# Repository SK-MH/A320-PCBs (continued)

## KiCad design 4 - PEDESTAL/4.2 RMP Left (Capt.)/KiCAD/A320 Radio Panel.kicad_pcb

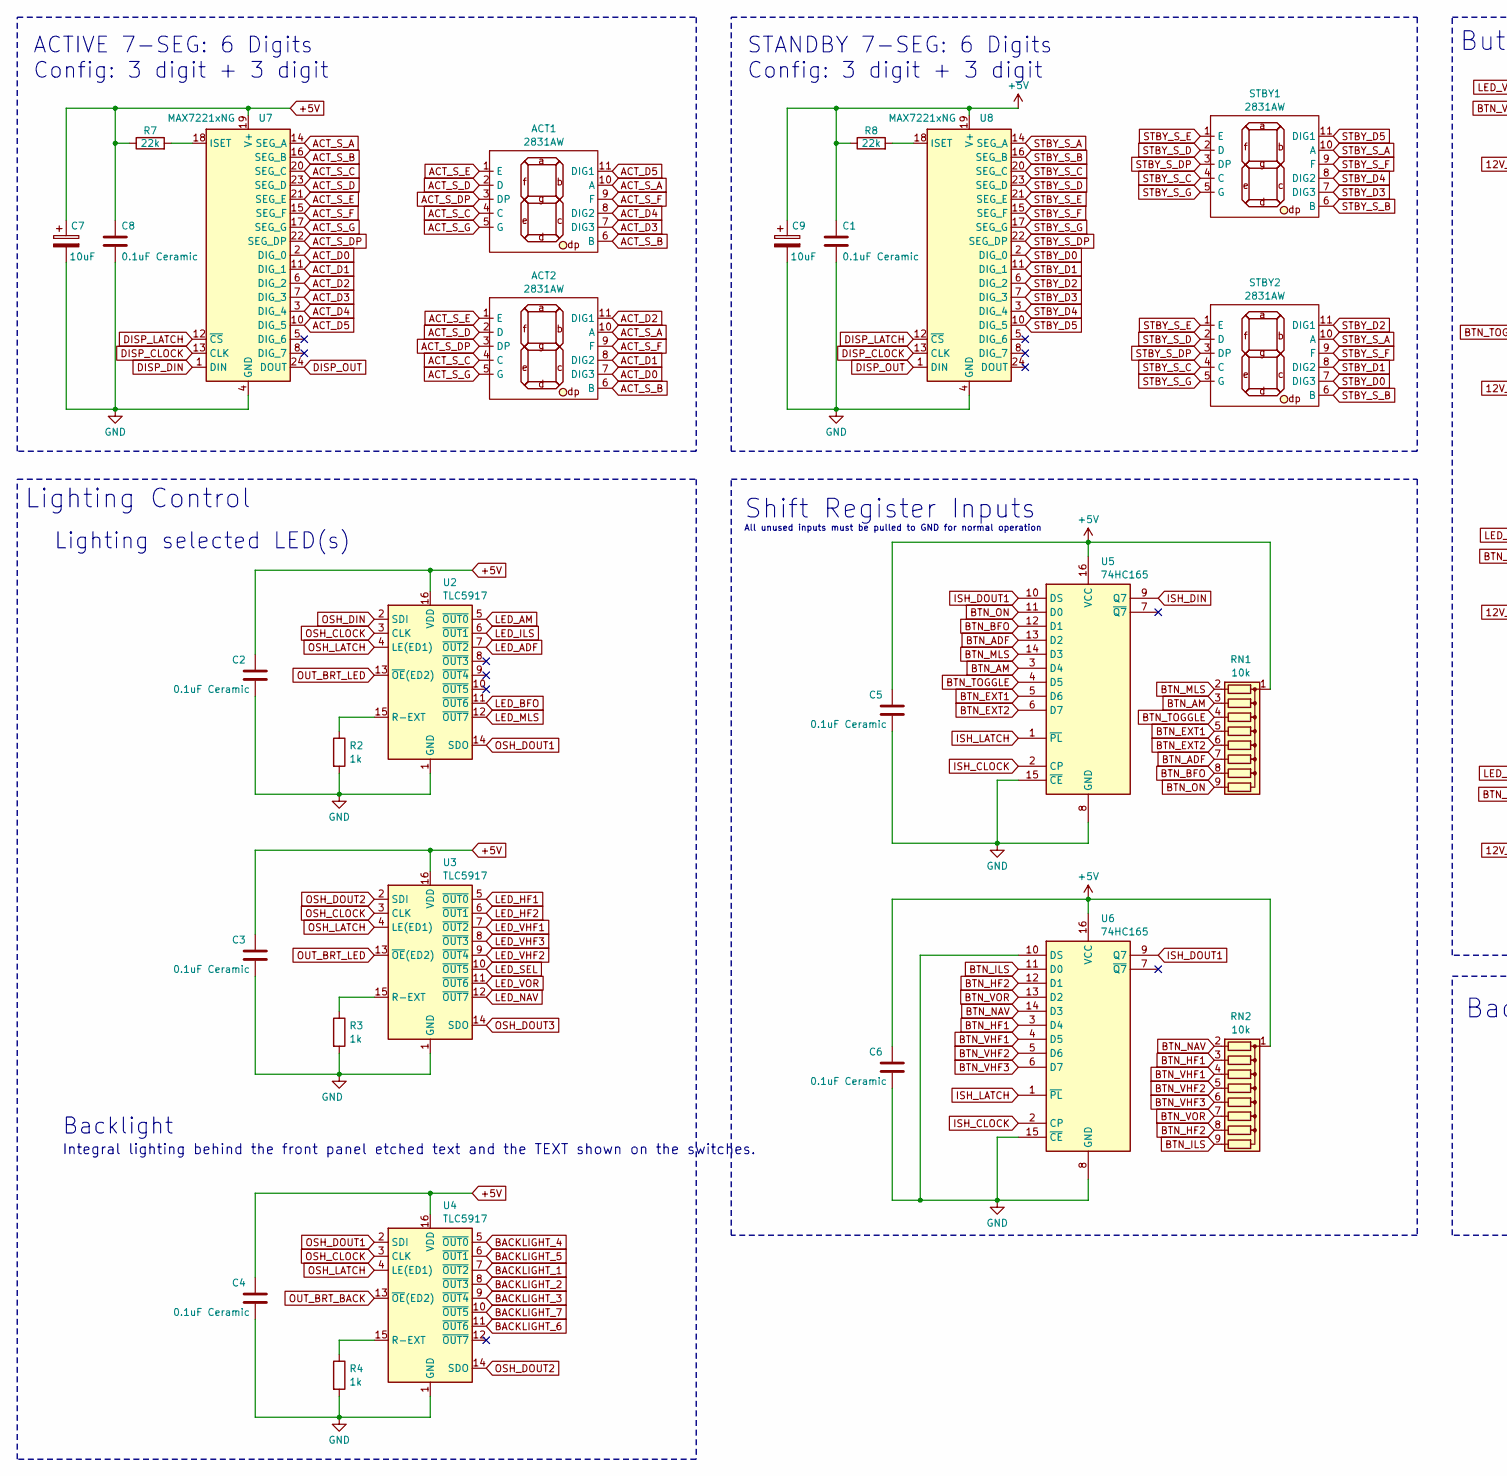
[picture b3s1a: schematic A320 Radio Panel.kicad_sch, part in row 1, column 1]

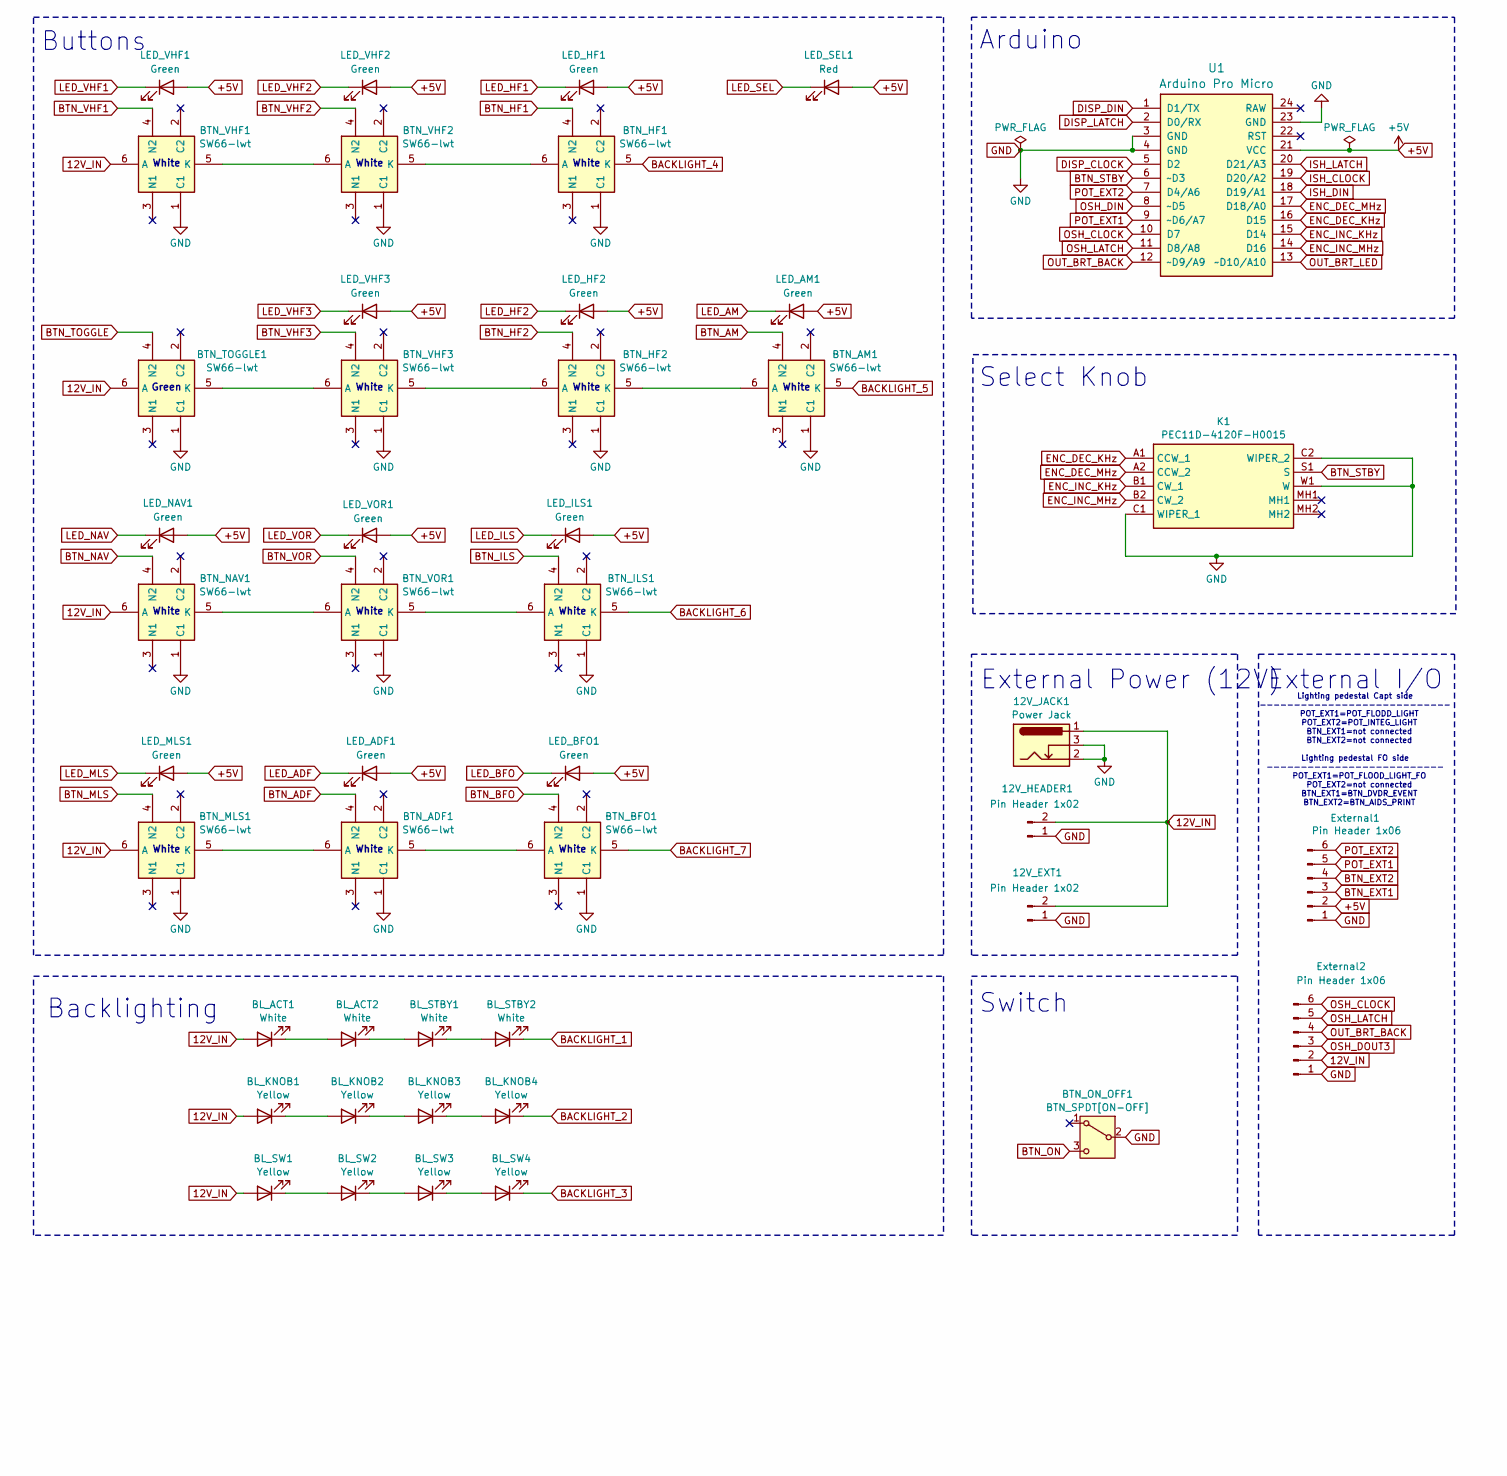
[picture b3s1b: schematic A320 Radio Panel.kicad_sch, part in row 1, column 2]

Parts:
12V_EXT1, 12V_HEADER1: Pin Header 1x02; JST_EH_B2B-EH-A_1x02_P2.50mm_Vertical
12V_JACK1: Power Jack; BarrelJack_Horizontal
ACT1, ACT2: 2831AW
BL_ACT1, BL_ACT2: White; LED_D3.0mm
BL_KNOB1, BL_KNOB2, BL_KNOB3, BL_KNOB4: Yellow; LED_D3.0mm
BL_STBY1, BL_STBY2: White; LED_D3.0mm
BL_SW1, BL_SW2, BL_SW3, BL_SW4: Yellow; LED_D3.0mm
BTN_ADF1: SW66-lwt
BTN_AM1: SW66-lwt
BTN_BFO1: SW66-lwt
BTN_HF1, BTN_HF2: SW66-lwt
BTN_ILS1: SW66-lwt
BTN_MLS1: SW66-lwt
BTN_NAV1: SW66-lwt
BTN_ON_OFF1: BTN_SPDT[ON-OFF]; T80-Z1
BTN_TOGGLE1: SW66-lwt
BTN_VHF1, BTN_VHF2, BTN_VHF3: SW66-lwt
BTN_VOR1: SW66-lwt
C1, C2, C3, C4, C5, C6, C8: 0.1uF Ceramic; C_Disc_D3.0mm_W1.6mm_P2.50mm
C7, C9: 10uF; CP_Radial_D4.0mm_P1.50mm
External1, External2: Pin Header 1x06; JST_EH_B6B-EH-A_1x06_P2.50mm_Vertical
K1: PEC11D-4120F-H0015; PEC11D4120FH0015; Mouser Part Number 652-PEC11D4120FH0015
LED_ADF1: Green; LED_D3.0mm
LED_AM1: Green; LED_D3.0mm
LED_BFO1: Green; LED_D3.0mm
LED_HF1, LED_HF2: Green; LED_D3.0mm
LED_ILS1: Green; LED_D3.0mm
LED_MLS1: Green; LED_D3.0mm
LED_NAV1: Green; LED_D3.0mm
LED_SEL1: Red; LED_D3.0mm
LED_VHF1, LED_VHF2, LED_VHF3: Green; LED_D3.0mm
LED_VOR1: Green; LED_D3.0mm
R2, R3, R4: 1k; R_Axial_DIN0204_L3.6mm_D1.6mm_P7.62mm_Horizontal
R7, R8: 22k; R_Axial_DIN0204_L3.6mm_D1.6mm_P7.62mm_Horizontal
RN1, RN2: 10k; R_Array_SIP9
STBY1, STBY2: 2831AW
U1: Arduino Pro Micro; Sparkfun_Pro_Micro
U2, U3, U4: TLC5917; DIP-16_W7.62mm
U5, U6: 74HC165; DIP-16_W7.62mm
U7, U8: MAX7221xNG; DIP-24_W7.62mm

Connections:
12V_IN: 12V_EXT1.2, 12V_HEADER1.2, 12V_JACK1.1, BL_ACT1.2 (A), BL_KNOB1.2 (A), BL_SW1.2 (A), BTN_MLS1.6 (A), BTN_NAV1.6 (A), BTN_TOGGLE1.6 (A), BTN_VHF1.6 (A), External2.2
+5V: C1.1, C2.1, C3.1, C4.1, C5.1, C6.1, C7.1, C8.1, C9.1, External1.2, LED_ADF1.2 (A), LED_AM1.2 (A), LED_BFO1.2 (A), LED_HF1.2 (A), LED_HF2.2 (A), LED_ILS1.2 (A), LED_MLS1.2 (A), LED_NAV1.2 (A), LED_SEL1.2 (A), LED_VHF1.2 (A), LED_VHF2.2 (A), LED_VHF3.2 (A), LED_VOR1.2 (A), R7.1, R8.1, RN1.1 (common), RN2.1 (common), U1.21 (VCC), U2.16 (VDD), U3.16 (VDD), U4.16 (VDD), U5.16 (VCC), U6.16 (VCC), U7.19 (V+), U8.19 (V+)
ACT_D0: ACT2.7 (DIG3), U7.2 (DIG_0)
ACT_D1: ACT2.8 (DIG2), U7.11 (DIG_1)
ACT_D2: ACT2.11 (DIG1), U7.6 (DIG_2)
ACT_D3: ACT1.7 (DIG3), U7.7 (DIG_3)
ACT_D4: ACT1.8 (DIG2), U7.3 (DIG_4)
ACT_D5: ACT1.11 (DIG1), U7.10 (DIG_5)
ACT_S_A: ACT1.10 (A), ACT2.10 (A), U7.14 (SEG_A)
ACT_S_B: ACT1.6 (B), ACT2.6 (B), U7.16 (SEG_B)
ACT_S_C: ACT1.4 (C), ACT2.4 (C), U7.20 (SEG_C)
ACT_S_D: ACT1.2 (D), ACT2.2 (D), U7.23 (SEG_D)
ACT_S_DP: ACT1.3 (DP), ACT2.3 (DP), U7.22 (SEG_DP)
ACT_S_E: ACT1.1 (E), ACT2.1 (E), U7.21 (SEG_E)
ACT_S_F: ACT1.9 (F), ACT2.9 (F), U7.15 (SEG_F)
ACT_S_G: ACT1.5 (G), ACT2.5 (G), U7.17 (SEG_G)
BACKLIGHT_1: BL_STBY2.1 (K), U4.7 (~OUT2)
BACKLIGHT_2: BL_KNOB4.1 (K), U4.8 (~OUT3)
BACKLIGHT_3: BL_SW4.1 (K), U4.9 (~OUT4)
BACKLIGHT_4: BTN_HF1.5 (K), U4.5 (~OUT0)
BACKLIGHT_5: BTN_AM1.5 (K), U4.6 (~OUT1)
BACKLIGHT_6: BTN_ILS1.5 (K), U4.11 (~OUT6)
BACKLIGHT_7: BTN_BFO1.5 (K), U4.10 (~OUT5)
BTN_ADF: BTN_ADF1.4 (N2), RN1.7 (R6), U5.13 (D2)
BTN_AM: BTN_AM1.4 (N2), RN1.3 (R2), U5.3 (D4)
BTN_BFO: BTN_BFO1.4 (N2), RN1.8 (R7), U5.12 (D1)
BTN_EXT1: External1.3, RN1.5 (R4), U5.5 (D6)
BTN_EXT2: External1.4, RN1.6 (R5), U5.6 (D7)
BTN_HF1: BTN_HF1.4 (N2), RN2.3 (R2), U6.3 (D4)
BTN_HF2: BTN_HF2.4 (N2), RN2.8 (R7), U6.12 (D1)
BTN_ILS: BTN_ILS1.4 (N2), RN2.9 (R8), U6.11 (D0)
BTN_MLS: BTN_MLS1.4 (N2), RN1.2 (R1), U5.14 (D3)
BTN_NAV: BTN_NAV1.4 (N2), RN2.2 (R1), U6.14 (D3)
BTN_ON: BTN_ON_OFF1.3 (C), RN1.9 (R8), U5.11 (D0)
BTN_STBY: K1.S1 (S), U1.6 (~D3)
BTN_TOGGLE: BTN_TOGGLE1.4 (N2), RN1.4 (R3), U5.4 (D5)
BTN_VHF1: BTN_VHF1.4 (N2), RN2.4 (R3), U6.4 (D5)
BTN_VHF2: BTN_VHF2.4 (N2), RN2.5 (R4), U6.5 (D6)
BTN_VHF3: BTN_VHF3.4 (N2), RN2.6 (R5), U6.6 (D7)
BTN_VOR: BTN_VOR1.4 (N2), RN2.7 (R6), U6.13 (D2)
DISP_CLOCK: U1.5 (D2), U7.13 (CLK), U8.13 (CLK)
DISP_DIN: U1.1 (D1/TX), U7.1 (DIN)
DISP_LATCH: U1.2 (D0/RX), U7.12 (~CS), U8.12 (~CS)
DISP_OUT: U7.24 (DOUT), U8.1 (DIN)
ENC_DEC_KHz: K1.A1 (CCW_1), U1.16 (D15)
ENC_DEC_MHz: K1.A2 (CCW_2), U1.17 (D18/A0)
ENC_INC_KHz: K1.B1 (CW_1), U1.15 (D14)
ENC_INC_MHz: K1.B2 (CW_2), U1.14 (D16)
GND: 12V_EXT1.1, 12V_HEADER1.1, 12V_JACK1.2, 12V_JACK1.3, BTN_ADF1.1 (C1), BTN_AM1.1 (C1), BTN_BFO1.1 (C1), BTN_HF1.1 (C1), BTN_HF2.1 (C1), BTN_ILS1.1 (C1), BTN_MLS1.1 (C1), BTN_NAV1.1 (C1), BTN_ON_OFF1.2 (B), BTN_TOGGLE1.1 (C1), BTN_VHF1.1 (C1), BTN_VHF2.1 (C1), BTN_VHF3.1 (C1), BTN_VOR1.1 (C1), C1.2, C2.2, C3.2, C4.2, C5.2, C6.2, C7.2, C8.2, C9.2, External1.1, External2.1, K1.C1 (WIPER_1), K1.C2 (WIPER_2), K1.W1 (W), R2.2, R3.2, R4.2, U1.3 (GND), U1.4 (GND), U1.23 (GND), U2.1 (GND), U3.1 (GND), U4.1 (GND), U5.8 (GND), U5.15 (~CE), U6.8 (GND), U6.10 (DS), U6.15 (~CE), U7.4 (GND), U7.9 (GND), U8.4 (GND), U8.9 (GND)
ISH_CLOCK: U1.19 (D20/A2), U5.2 (CP), U6.2 (CP)
ISH_DIN: U1.18 (D19/A1), U5.9 (Q7)
ISH_DOUT1: U5.10 (DS), U6.9 (Q7)
ISH_LATCH: U1.20 (D21/A3), U5.1 (~PL), U6.1 (~PL)
LED_ADF: LED_ADF1.1 (K), U2.7 (~OUT2)
LED_AM: LED_AM1.1 (K), U2.5 (~OUT0)
LED_BFO: LED_BFO1.1 (K), U2.11 (~OUT6)
LED_HF1: LED_HF1.1 (K), U3.5 (~OUT0)
LED_HF2: LED_HF2.1 (K), U3.6 (~OUT1)
LED_ILS: LED_ILS1.1 (K), U2.6 (~OUT1)
LED_MLS: LED_MLS1.1 (K), U2.12 (~OUT7)
LED_NAV: LED_NAV1.1 (K), U3.12 (~OUT7)
LED_SEL: LED_SEL1.1 (K), U3.10 (~OUT5)
LED_VHF1: LED_VHF1.1 (K), U3.7 (~OUT2)
LED_VHF2: LED_VHF2.1 (K), U3.9 (~OUT4)
LED_VHF3: LED_VHF3.1 (K), U3.8 (~OUT3)
LED_VOR: LED_VOR1.1 (K), U3.11 (~OUT6)
unnamed: BL_ACT1.1 (K), BL_ACT2.2 (A)
unnamed: BL_ACT2.1 (K), BL_STBY1.2 (A)
unnamed: BL_KNOB1.1 (K), BL_KNOB2.2 (A)
unnamed: BL_KNOB2.1 (K), BL_KNOB3.2 (A)
unnamed: BL_KNOB3.1 (K), BL_KNOB4.2 (A)
unnamed: BL_STBY1.1 (K), BL_STBY2.2 (A)
unnamed: BL_SW1.1 (K), BL_SW2.2 (A)
unnamed: BL_SW2.1 (K), BL_SW3.2 (A)
unnamed: BL_SW3.1 (K), BL_SW4.2 (A)
unnamed: BTN_ADF1.6 (A), BTN_MLS1.5 (K)
unnamed: BTN_ADF1.5 (K), BTN_BFO1.6 (A)
unnamed: BTN_AM1.6 (A), BTN_HF2.5 (K)
unnamed: BTN_HF1.6 (A), BTN_VHF2.5 (K)
unnamed: BTN_HF2.6 (A), BTN_VHF3.5 (K)
unnamed: BTN_ILS1.6 (A), BTN_VOR1.5 (K)
unnamed: BTN_NAV1.5 (K), BTN_VOR1.6 (A)
unnamed: BTN_TOGGLE1.5 (K), BTN_VHF3.6 (A)
unnamed: BTN_VHF1.5 (K), BTN_VHF2.6 (A)
unnamed: R2.1, U2.15 (R-EXT)
unnamed: R3.1, U3.15 (R-EXT)
unnamed: R4.1, U4.15 (R-EXT)
unnamed: R7.2, U7.18 (ISET)
unnamed: R8.2, U8.18 (ISET)
OSH_CLOCK: External2.6, U1.10 (D7), U2.3 (CLK), U3.3 (CLK), U4.3 (CLK)
OSH_DIN: U1.8 (~D5), U2.2 (SDI)
OSH_DOUT1: U2.14 (SDO), U4.2 (SDI)
OSH_DOUT2: U3.2 (SDI), U4.14 (SDO)
OSH_DOUT3: External2.3, U3.14 (SDO)
OSH_LATCH: External2.5, U1.11 (D8/A8), U2.4 (LE(ED1)), U3.4 (LE(ED1)), U4.4 (LE(ED1))
OUT_BRT_BACK: External2.4, U1.12 (~D9/A9), U4.13 (~OE(ED2))
OUT_BRT_LED: U1.13 (~D10/A10), U2.13 (~OE(ED2)), U3.13 (~OE(ED2))
POT_EXT1: External1.5, U1.9 (~D6/A7)
POT_EXT2: External1.6, U1.7 (D4/A6)
STBY_D0: STBY2.7 (DIG3), U8.2 (DIG_0)
STBY_D1: STBY2.8 (DIG2), U8.11 (DIG_1)
STBY_D2: STBY2.11 (DIG1), U8.6 (DIG_2)
STBY_D3: STBY1.7 (DIG3), U8.7 (DIG_3)
STBY_D4: STBY1.8 (DIG2), U8.3 (DIG_4)
STBY_D5: STBY1.11 (DIG1), U8.10 (DIG_5)
STBY_S_A: STBY1.10 (A), STBY2.10 (A), U8.14 (SEG_A)
STBY_S_B: STBY1.6 (B), STBY2.6 (B), U8.16 (SEG_B)
STBY_S_C: STBY1.4 (C), STBY2.4 (C), U8.20 (SEG_C)
STBY_S_D: STBY1.2 (D), STBY2.2 (D), U8.23 (SEG_D)
STBY_S_DP: STBY1.3 (DP), STBY2.3 (DP), U8.22 (SEG_DP)
STBY_S_E: STBY1.1 (E), STBY2.1 (E), U8.21 (SEG_E)
STBY_S_F: STBY1.9 (F), STBY2.9 (F), U8.15 (SEG_F)
STBY_S_G: STBY1.5 (G), STBY2.5 (G), U8.17 (SEG_G)

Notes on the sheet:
White
STANDBY 7-SEG: 6 Digits Config: 3 digit + 3 digit
Lighting selected LED(s)
Backlight
Buttons
Shift Register Inputs
Lighting Control
External I/O
Green
Integral lighting behind the front panel etched text and the TEXT shown on the switches.
Lighting pedestal Capt side ---------------------------- POT_EXT1=POT_FLODD_LIGHT POT_EXT2=POT_INTEG_LIGHT BTN_EXT1=not connected BTN_EXT2=not connected Lighting pedestal FO side -------------------------- POT_EXT1=POT_FLOOD_LIGHT_FO POT_EXT2=not connected BTN_EXT1=BTN_DVDR_EVENT BTN_EXT2=BTN_AIDS_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
Arduino
All unused inputs must be pulled to GND for normal operation
Switch
Select Knob
ACTIVE 7-SEG: 6 Digits Config: 3 digit + 3 digit
External Power (12V)
Backlighting

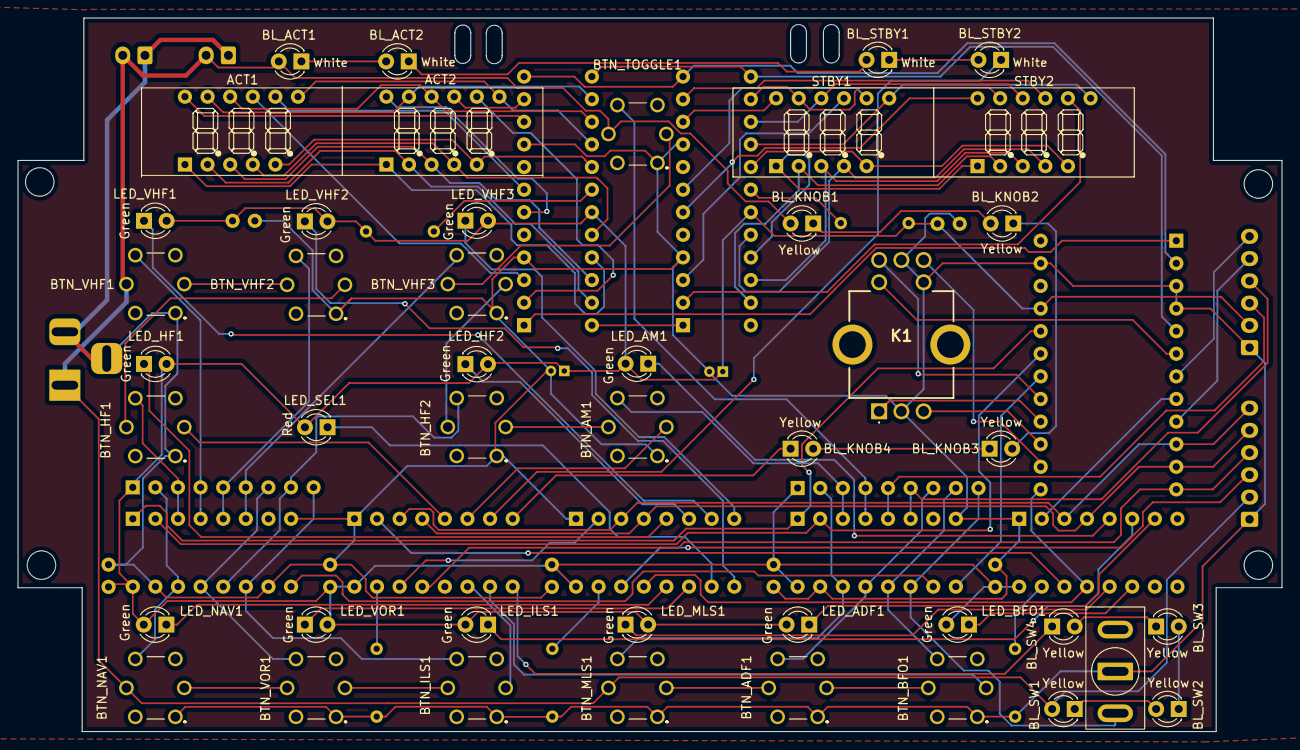
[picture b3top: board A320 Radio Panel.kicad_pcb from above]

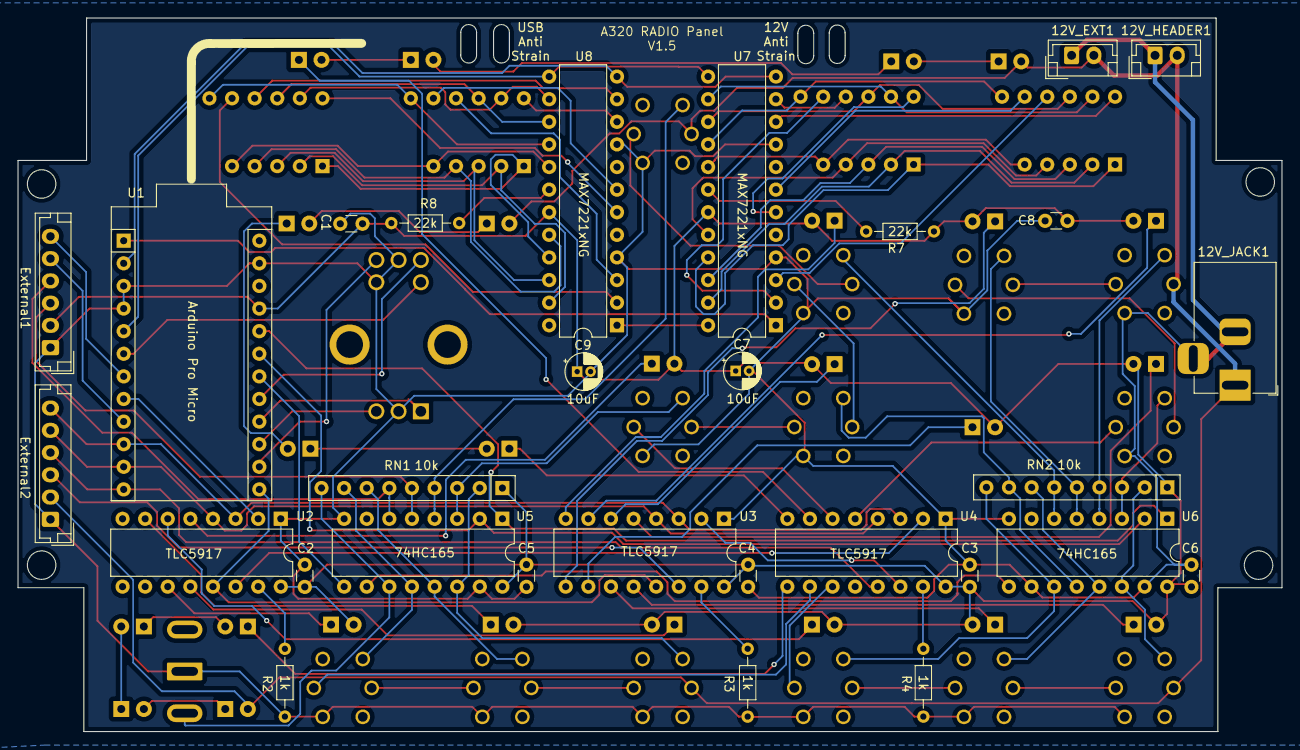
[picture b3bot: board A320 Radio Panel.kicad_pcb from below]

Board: 2 copper layers, 142.0 x 80.2 mm, 73 parts (29 on the bottom side), 113 nets.

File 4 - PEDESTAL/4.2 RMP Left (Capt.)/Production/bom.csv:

Designator,Footprint,Quantity,Value,LCSC Part #
"12V_EXT1, 12V_HEADER1",JST_EH_B2B-EH-A_1x02_P2.50mm_Vertical,2,Pin Header 1x02,
12V_JACK1,BarrelJack_Horizontal,1,Power Jack,
"ACT1, ACT2, STBY1, STBY2",2831AW,4,2831AW,
"BL_ACT1, BL_ACT2, BL_STBY1, BL_STBY2",LED_D3.0mm,4,White,
"BL_KNOB1, BL_KNOB2, BL_KNOB3, BL_KNOB4, BL_SW1, BL_SW2, BL_SW3, BL_SW4",LED_D3.0mm,8,Yellow,
"BTN_ADF1, BTN_AM1, BTN_BFO1, BTN_HF1, BTN_HF2, BTN_ILS1, BTN_MLS1, BTN_NAV1, BTN_TOGGLE1, BTN_VHF1, BTN_VHF2, BTN_VHF3, BTN_VOR1",SW66-lwt,13,SW66-lwt,
BTN_ON_OFF1,T80-Z1,1,BTN_SPDT[ON-OFF],
"C1, C2, C3, C4, C5, C6, C8",C_Disc_D3.0mm_W1.6mm_P2.50mm,7,0.1uF Ceramic,
"C7, C9",CP_Radial_D4.0mm_P1.50mm,2,10uF,
"External1, External2",JST_EH_B6B-EH-A_1x06_P2.50mm_Vertical,2,Pin Header 1x06,
K1,PEC11D4120FH0015,1,PEC11D-4120F-H0015,
"LED_ADF1, LED_AM1, LED_BFO1, LED_HF1, LED_HF2, LED_ILS1, LED_MLS1, LED_NAV1, LED_VHF1, LED_VHF2, LED_VHF3, LED_VOR1",LED_D3.0mm,12,Green,
LED_SEL1,LED_D3.0mm,1,Red,
"R2, R3, R4",R_Axial_DIN0204_L3.6mm_D1.6mm_P7.62mm_Horizontal,3,1k,
"R7, R8",R_Axial_DIN0204_L3.6mm_D1.6mm_P7.62mm_Horizontal,2,22k,
"RN1, RN2",R_Array_SIP9,2,10k,
U1,Sparkfun_Pro_Micro,1,Arduino Pro Micro,
"U2, U3, U4",DIP-16_W7.62mm,3,TLC5917,
"U5, U6",DIP-16_W7.62mm,2,74HC165,
"U7, U8",DIP-24_W7.62mm,2,MAX7221xNG,

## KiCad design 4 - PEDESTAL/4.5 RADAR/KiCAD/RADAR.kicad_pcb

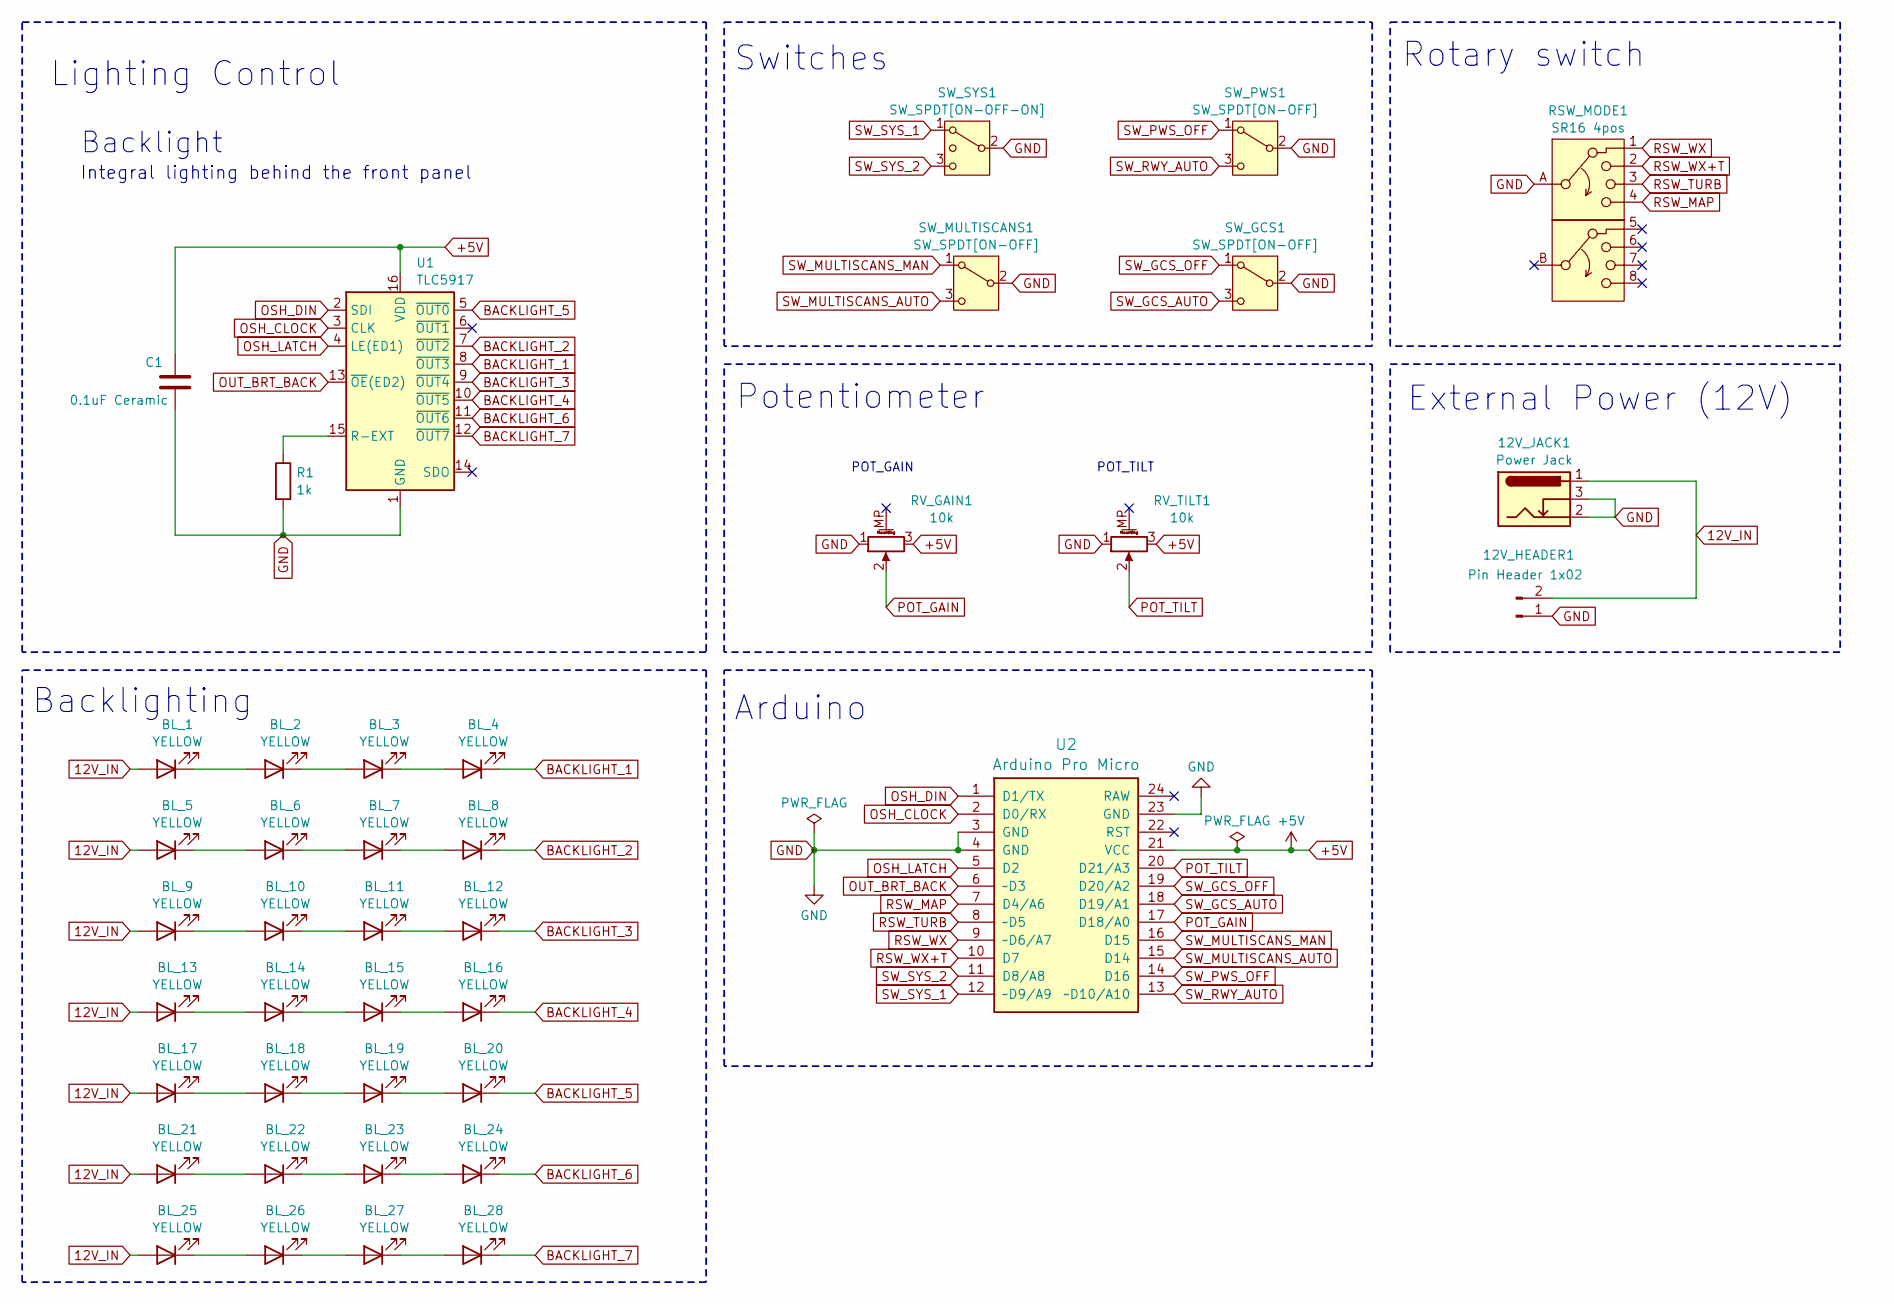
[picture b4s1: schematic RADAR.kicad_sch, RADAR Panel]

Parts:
12V_HEADER1: Pin Header 1x02; JST_EH_B2B-EH-A_1x02_P2.50mm_Vertical
12V_JACK1: Power Jack; BarrelJack_Horizontal
BL_1, BL_2, BL_3, BL_4, BL_5, BL_6, BL_7, BL_8, BL_9, BL_10, BL_11, BL_12, BL_13, BL_14, BL_15, BL_16, BL_17, BL_18, BL_19, BL_20, BL_21, BL_22, BL_23, BL_24, BL_25, BL_26, BL_27, BL_28: YELLOW; LED_D3.0mm
C1: 0.1uF Ceramic; C_Disc_D3.0mm_W1.6mm_P2.50mm
R1: 1k; R_Axial_DIN0204_L3.6mm_D1.6mm_P5.08mm_Horizontal
RSW_MODE1: SR16 4pos; SR16-AB
RV_GAIN1: 10k; Potentiometer_Alps_RK09K_Single_Vertical
RV_TILT1: 10k; Potentiometer_Alps_RK09K_Single_Vertical
SW_GCS1: SW_SPDT[ON-OFF]; T80-Z1
SW_MULTISCANS1: SW_SPDT[ON-OFF]; T80-Z1
SW_PWS1: SW_SPDT[ON-OFF]; T80-Z1
SW_SYS1: SW_SPDT[ON-OFF-ON]; T80-Z1
U1: TLC5917; DIP-16_W7.62mm
U2: Arduino Pro Micro; Sparkfun_Pro_Micro

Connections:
12V_IN: 12V_HEADER1.2, 12V_JACK1.1, BL_1.2 (A), BL_5.2 (A), BL_9.2 (A), BL_13.2 (A), BL_17.2 (A), BL_21.2 (A), BL_25.2 (A)
+5V: C1.1, RV_GAIN1.3, RV_TILT1.3, U1.16 (VDD), U2.21 (VCC)
BACKLIGHT_1: BL_4.1 (K), U1.8 (~OUT3)
BACKLIGHT_2: BL_8.1 (K), U1.7 (~OUT2)
BACKLIGHT_3: BL_12.1 (K), U1.9 (~OUT4)
BACKLIGHT_4: BL_16.1 (K), U1.10 (~OUT5)
BACKLIGHT_5: BL_20.1 (K), U1.5 (~OUT0)
BACKLIGHT_6: BL_24.1 (K), U1.11 (~OUT6)
BACKLIGHT_7: BL_28.1 (K), U1.12 (~OUT7)
GND: 12V_HEADER1.1, 12V_JACK1.2, 12V_JACK1.3, C1.2, R1.2, RSW_MODE1.A, RV_GAIN1.1, RV_TILT1.1, SW_GCS1.2 (B), SW_MULTISCANS1.2 (B), SW_PWS1.2 (B), SW_SYS1.2 (3), U1.1 (GND), U2.3 (GND), U2.4 (GND), U2.23 (GND)
unnamed: BL_1.1 (K), BL_2.2 (A)
unnamed: BL_2.1 (K), BL_3.2 (A)
unnamed: BL_3.1 (K), BL_4.2 (A)
unnamed: BL_5.1 (K), BL_6.2 (A)
unnamed: BL_6.1 (K), BL_7.2 (A)
unnamed: BL_7.1 (K), BL_8.2 (A)
unnamed: BL_9.1 (K), BL_10.2 (A)
unnamed: BL_10.1 (K), BL_11.2 (A)
unnamed: BL_11.1 (K), BL_12.2 (A)
unnamed: BL_13.1 (K), BL_14.2 (A)
unnamed: BL_14.1 (K), BL_15.2 (A)
unnamed: BL_15.1 (K), BL_16.2 (A)
unnamed: BL_17.1 (K), BL_18.2 (A)
unnamed: BL_18.1 (K), BL_19.2 (A)
unnamed: BL_19.1 (K), BL_20.2 (A)
unnamed: BL_21.1 (K), BL_22.2 (A)
unnamed: BL_22.1 (K), BL_23.2 (A)
unnamed: BL_23.1 (K), BL_24.2 (A)
unnamed: BL_25.1 (K), BL_26.2 (A)
unnamed: BL_26.1 (K), BL_27.2 (A)
unnamed: BL_27.1 (K), BL_28.2 (A)
unnamed: R1.1, U1.15 (R-EXT)
OSH_CLOCK: U1.3 (CLK), U2.2 (D0/RX)
OSH_DIN: U1.2 (SDI), U2.1 (D1/TX)
OSH_LATCH: U1.4 (LE(ED1)), U2.5 (D2)
OUT_BRT_BACK: U1.13 (~OE(ED2)), U2.6 (~D3)
POT_GAIN: RV_GAIN1.2, U2.17 (D18/A0)
POT_TILT: RV_TILT1.2, U2.20 (D21/A3)
RSW_MAP: RSW_MODE1.4, U2.7 (D4/A6)
RSW_TURB: RSW_MODE1.3, U2.8 (~D5)
RSW_WX: RSW_MODE1.1, U2.9 (~D6/A7)
RSW_WX+T: RSW_MODE1.2, U2.10 (D7)
SW_GCS_AUTO: SW_GCS1.3 (C), U2.18 (D19/A1)
SW_GCS_OFF: SW_GCS1.1 (A), U2.19 (D20/A2)
SW_MULTISCANS_AUTO: SW_MULTISCANS1.3 (C), U2.15 (D14)
SW_MULTISCANS_MAN: SW_MULTISCANS1.1 (A), U2.16 (D15)
SW_PWS_OFF: SW_PWS1.1 (A), U2.14 (D16)
SW_RWY_AUTO: SW_PWS1.3 (C), U2.13 (~D10/A10)
SW_SYS_1: SW_SYS1.1, U2.12 (~D9/A9)
SW_SYS_2: SW_SYS1.3 (4), U2.11 (D8/A8)

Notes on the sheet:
POT_TILT
Integral lighting behind the front panel
Potentiometer
Switches
Arduino
Rotary switch
Backlighting
POT_GAIN
Backlight
Lighting Control
External Power (12V)

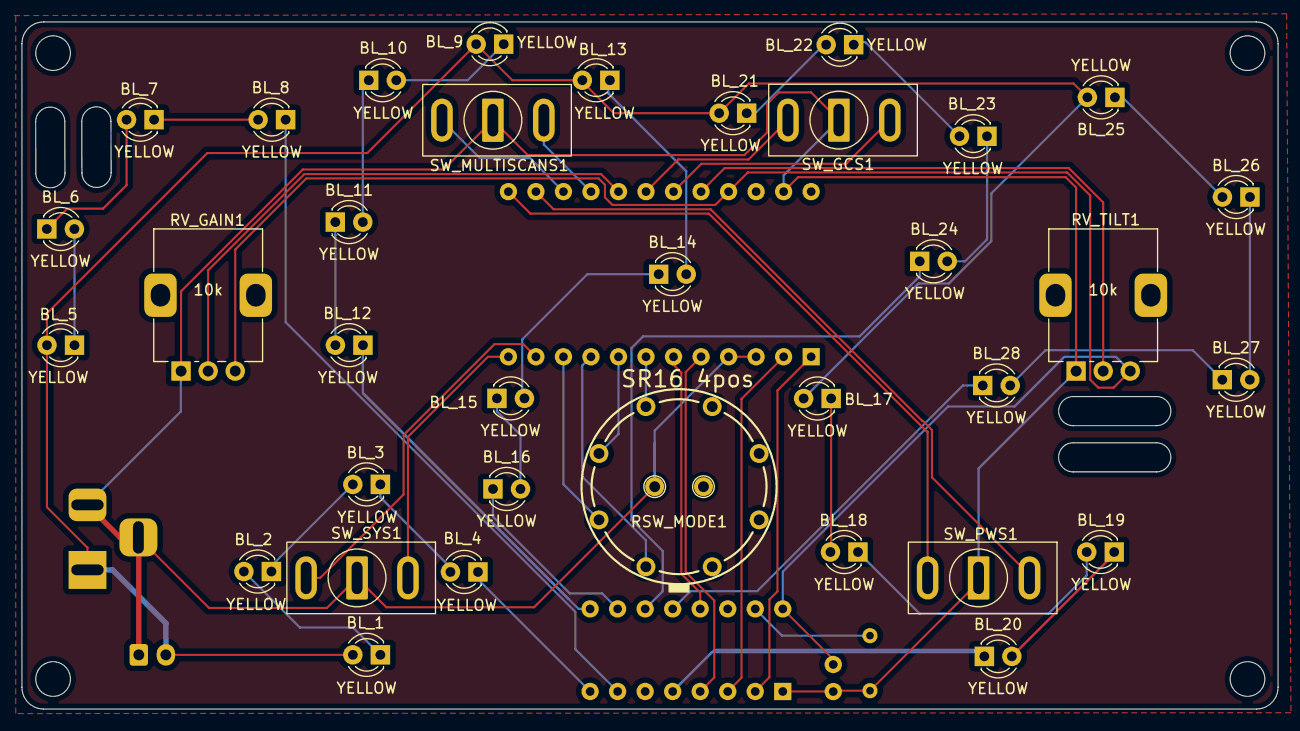
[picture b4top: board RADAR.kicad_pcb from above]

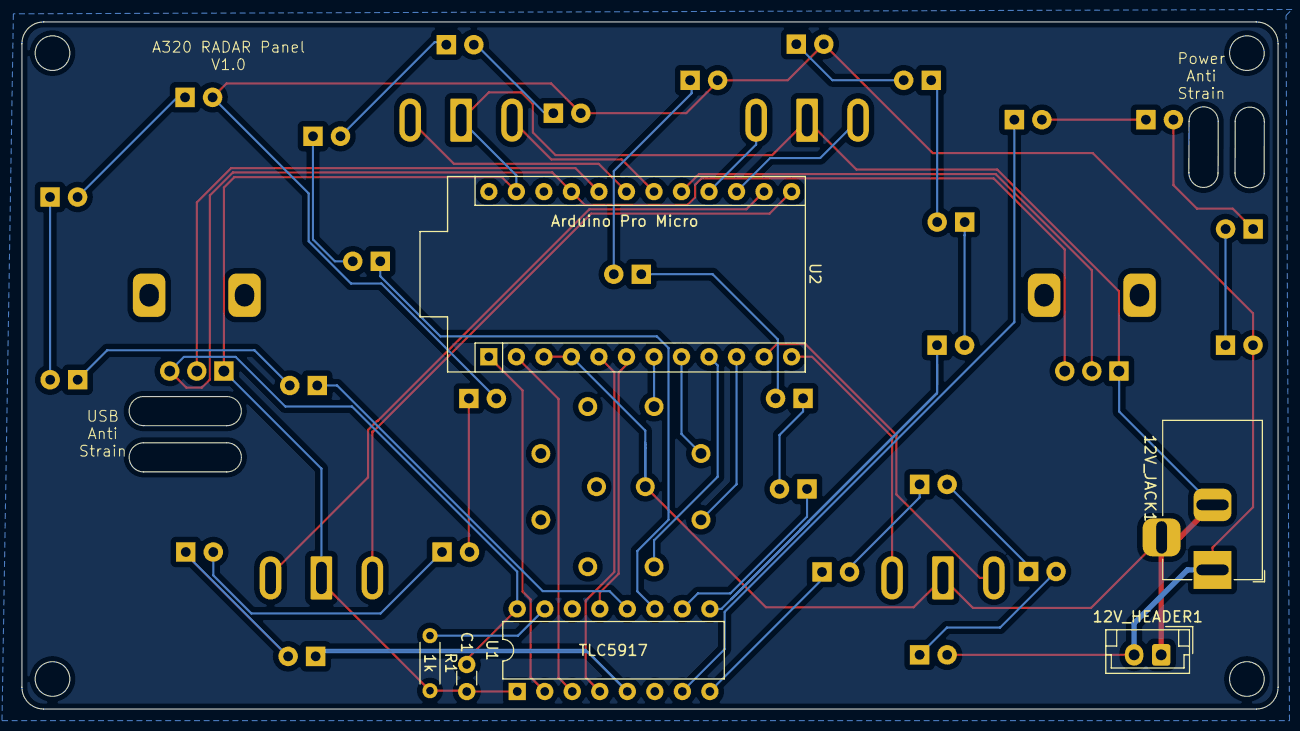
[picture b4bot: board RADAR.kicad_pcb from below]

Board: 2 copper layers, 115.9 x 63.4 mm, 41 parts (6 on the bottom side), 50 nets.

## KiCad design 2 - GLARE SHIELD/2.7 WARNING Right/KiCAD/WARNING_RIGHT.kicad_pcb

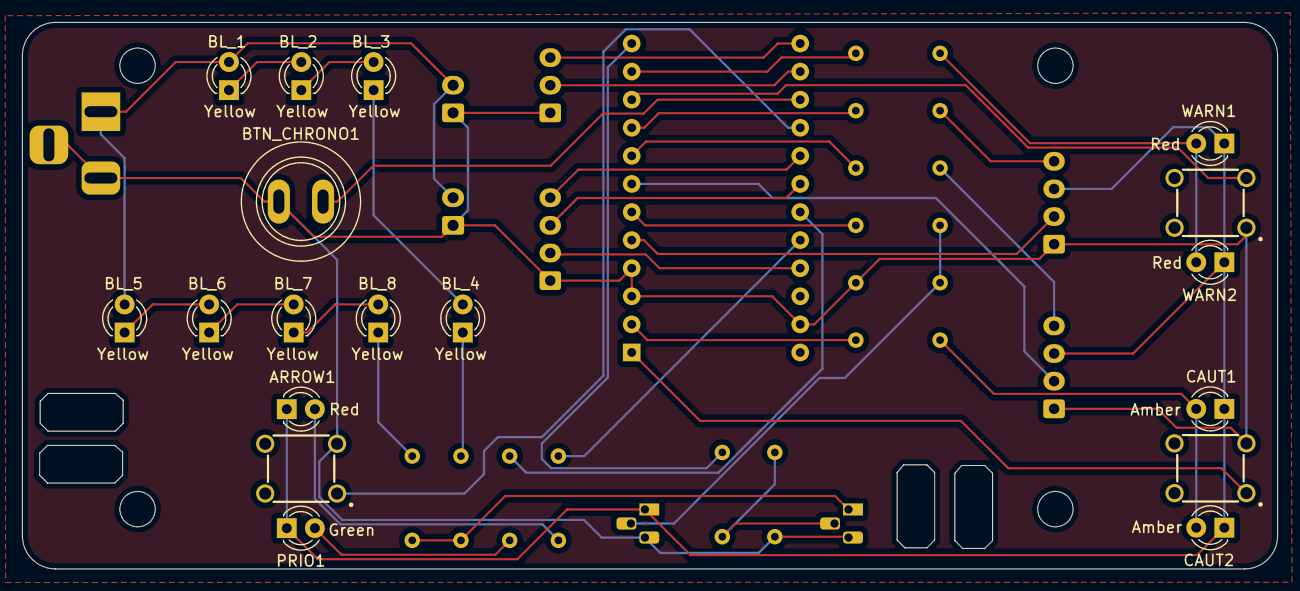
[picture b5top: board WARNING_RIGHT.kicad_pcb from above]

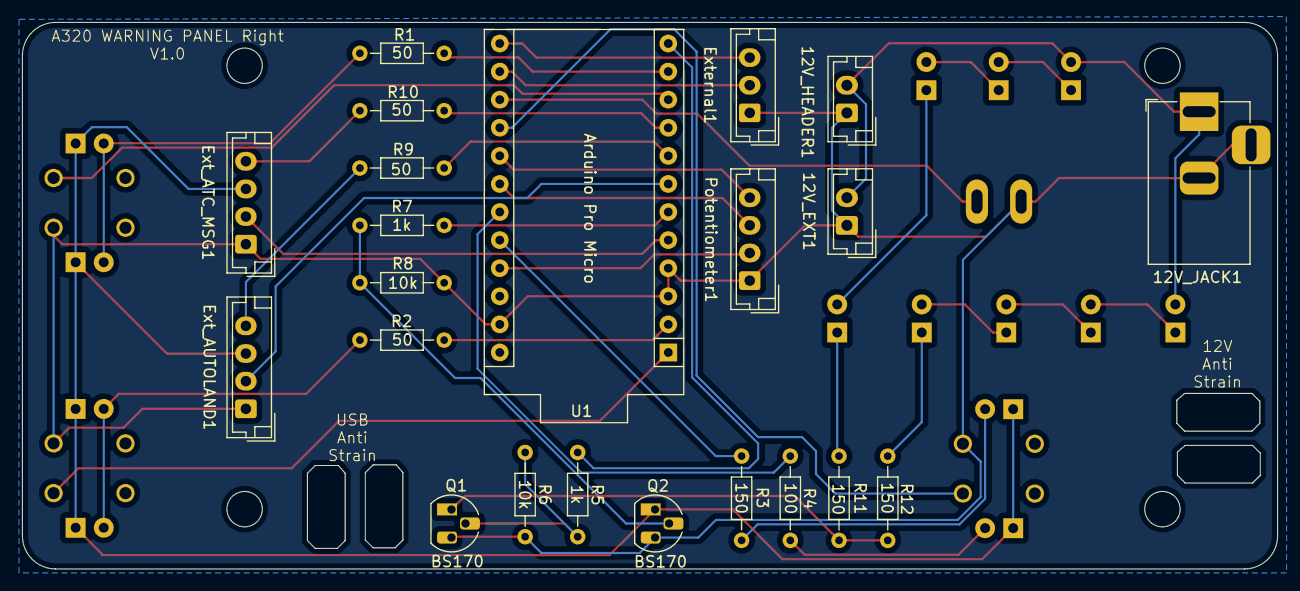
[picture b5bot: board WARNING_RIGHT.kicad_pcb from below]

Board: 2 copper layers, 113.5 x 49.4 mm, 40 parts (22 on the bottom side), 39 nets.

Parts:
12V_EXT1, 12V_HEADER1: Pin Header 1x02; JST_EH_B2B-EH-A_1x02_P2.50mm_Vertical
12V_JACK1: Power Jack; BarrelJack_Horizontal
ARROW1: Red; LED_D3.0mm
BL_1, BL_2, BL_3, BL_4, BL_5, BL_6, BL_7, BL_8: Yellow; LED_D3.0mm
BTN_CAUT1: B3F-1055; B3F1000
BTN_CHRONO1: Push Button; SW-Push
BTN_SIDESTICK1: B3F-1055; B3F1000
BTN_WARN1: B3F-1055; B3F1000
CAUT1, CAUT2: Amber; LED_D3.0mm
Ext_ATC_MSG1: Pin Header 1x04; JST_EH_B4B-EH-A_1x04_P2.50mm_Vertical
Ext_AUTOLAND1: Pin Header 1x04; JST_EH_B4B-EH-A_1x04_P2.50mm_Vertical
External1: Pin Header 1x03; JST_EH_B3B-EH-A_1x03_P2.50mm_Vertical
PRIO1: Green; LED_D3.0mm
Potentiometer1: Pin Header 1x04; JST_EH_B4B-EH-A_1x04_P2.50mm_Vertical
Q1, Q2: BS170; TO-92_HandSolder
R1, R2, R9, R10: 50; R_Axial_DIN0204_L3.6mm_D1.6mm_P7.62mm_Horizontal
R3, R11, R12: 150; R_Axial_DIN0204_L3.6mm_D1.6mm_P7.62mm_Horizontal
R4: 100; R_Axial_DIN0204_L3.6mm_D1.6mm_P7.62mm_Horizontal
R5, R7: 1k; R_Axial_DIN0204_L3.6mm_D1.6mm_P7.62mm_Horizontal
R6, R8: 10k; R_Axial_DIN0204_L3.6mm_D1.6mm_P7.62mm_Horizontal
U1: Arduino Pro Micro; Sparkfun_Pro_Micro
WARN1, WARN2: Red; LED_D3.0mm

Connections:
12V_IN: 12V_EXT1.2, 12V_HEADER1.2, 12V_JACK1.1, BL_1.2 (A), BL_5.2 (A)
+5V: Potentiometer1.2, U1.21 (VCC)
ARROW: R3.1, U1.20 (D21/A3)
ATC_MSG: R10.2, U1.9 (~D6/A7)
AUTOLAND: R9.2, U1.8 (~D5)
BACKLIGHT_GND: Q1.1 (D), R11.2, R12.2
BTN_ATC_MSG: Ext_ATC_MSG1.2, U1.5 (D2)
BTN_AUTOLAND: Ext_AUTOLAND1.2, U1.7 (D4/A6)
BTN_CAUT: BTN_CAUT1.1, U1.1 (D1/TX)
BTN_CHRONO: BTN_CHRONO1.1, U1.15 (D14)
BTN_SIDESTICK: BTN_SIDESTICK1.1, U1.16 (D15)
BTN_WARN: BTN_WARN1.3, U1.10 (D7)
CAUT: R2.1, U1.2 (D0/RX)
EXT1: External1.2, U1.14 (D16)
EXT2: External1.3, U1.13 (~D10/A10)
GND: 12V_EXT1.1, 12V_HEADER1.1, 12V_JACK1.2, 12V_JACK1.3, BTN_CAUT1.3, BTN_CHRONO1.2, BTN_SIDESTICK1.3, BTN_WARN1.1, Ext_ATC_MSG1.1, Ext_AUTOLAND1.1, External1.1, Potentiometer1.1, Q1.3 (S), Q2.3 (S), R6.1, R8.1, U1.3 (GND), U1.4 (GND), U1.23 (GND)
LED_GND: ARROW1.1 (K), CAUT1.1 (K), CAUT2.1 (K), Ext_ATC_MSG1.3, Ext_AUTOLAND1.3, PRIO1.1 (K), Q2.1 (D), WARN1.1 (K), WARN2.1 (K)
unnamed: ARROW1.2 (A), R3.2
unnamed: BL_1.1 (K), BL_2.2 (A)
unnamed: BL_2.1 (K), BL_3.2 (A)
unnamed: BL_3.1 (K), BL_4.2 (A)
unnamed: BL_4.1 (K), R11.1
unnamed: BL_5.1 (K), BL_6.2 (A)
unnamed: BL_6.1 (K), BL_7.2 (A)
unnamed: BL_7.1 (K), BL_8.2 (A)
unnamed: BL_8.1 (K), R12.1
unnamed: CAUT1.2 (A), CAUT2.2 (A), R2.2
unnamed: Ext_ATC_MSG1.4, R10.1
unnamed: Ext_AUTOLAND1.4, R9.1
unnamed: PRIO1.2 (A), R4.2
unnamed: Q1.2 (G), R5.2, R6.2
unnamed: Q2.2 (G), R7.2, R8.2
unnamed: R1.2, WARN1.2 (A), WARN2.2 (A)
OUT_BRT_BACK: R5.1, U1.12 (~D9/A9)
OUT_BRT_LED: R7.1, U1.6 (~D3)
POT1: Potentiometer1.3, U1.18 (D19/A1)
POT2: Potentiometer1.4, U1.17 (D18/A0)
PRIO: R4.1, U1.19 (D20/A2)
WARN: R1.1, U1.11 (D8/A8)

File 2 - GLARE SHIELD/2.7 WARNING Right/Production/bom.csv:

Designator,Footprint,Quantity,Value,LCSC Part #
"12V_EXT1, 12V_HEADER1",JST_EH_B2B-EH-A_1x02_P2.50mm_Vertical,2,Pin Header 1x02,
12V_JACK1,BarrelJack_Horizontal,1,Power Jack,
"ARROW1, WARN1, WARN2",LED_D3.0mm,3,Red,
"BL_1, BL_2, BL_3, BL_4, BL_5, BL_6, BL_7, BL_8",LED_D3.0mm,8,Yellow,
"BTN_CAUT1, BTN_SIDESTICK1, BTN_WARN1",B3F1000,3,B3F-1055,
BTN_CHRONO1,SW-Push,1,Push Button,
"CAUT1, CAUT2",LED_D3.0mm,2,Amber,
"Ext_ATC_MSG1, Ext_AUTOLAND1, Potentiometer1",JST_EH_B4B-EH-A_1x04_P2.50mm_Vertical,3,Pin Header 1x04,
External1,JST_EH_B3B-EH-A_1x03_P2.50mm_Vertical,1,Pin Header 1x03,
PRIO1,LED_D3.0mm,1,Green,
"Q1, Q2",TO-92_HandSolder,2,BS170,
"R1, R10, R2, R9",R_Axial_DIN0204_L3.6mm_D1.6mm_P7.62mm_Horizontal,4,50,
"R11, R12, R3",R_Axial_DIN0204_L3.6mm_D1.6mm_P7.62mm_Horizontal,3,150,
R4,R_Axial_DIN0204_L3.6mm_D1.6mm_P7.62mm_Horizontal,1,100,
"R5, R7",R_Axial_DIN0204_L3.6mm_D1.6mm_P7.62mm_Horizontal,2,1k,
"R6, R8",R_Axial_DIN0204_L3.6mm_D1.6mm_P7.62mm_Horizontal,2,10k,
U1,Sparkfun_Pro_Micro,1,Arduino Pro Micro,
